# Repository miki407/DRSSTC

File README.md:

# Welcome
> **WARNING:**
> This project has not been tested yet. I cant guarantee that any of the circuits, PCBs, 3d models work or are accurate.

>This project is incomplete. The README isn't finished yet.

## Overview

This project is a tesla coil, DRSSTC to be more exact. Tesla coils are devices capable of generating extreme voltages that can be lethal if not operated correctly. 
> **Warning:** This project deals with high voltages. Replicate at your own risk.
 
 It is designed with a full bridge inverter connected to a MMC as the primary tank capacitor. This full bridge uses 4 parallel IGBT pairs driven by a single GDT. This GDT connects to the control circuit. Using a MIDI interrupter this coil has the ability to play music.

## Physical Design

The coil is designed with a skeleton topload and a vertical breakout point located in the middle of the topload. The primary coil is a pancake with a ground ring that is meant to protect it from flashover from topload.
>Note: The grounding ring is shouldn't be closed loop like shown in the image. This would short circuit the induced current and cause large current draw and energy loss.

## Circuit
The circuit for the control circuit and inverter are inspired by the UD2.7c and EasyBridge made by [Loneoceans](https://www.loneoceans.com/labs/index.htm). These circuits have been modified to fit the needs of this project.
The interactive BOM of these boards are here:
[Inverter](https://htmlpreview.github.io/?https://github.com/miki407/DRSSTC/blob/main/Full%20Bridge/Full%20Bridge/bom/ibom.html)
[Control circuit](https://htmlpreview.github.io/?https://github.com/miki407/DRSSTC/blob/main/Controller/DRSSTC%20controller/bom/ibom.html)

## Future additions

* Polyphonic MIDI interrupter
* Testing data
* Assembly guide
* Full BOM 

## Mistakes and Suggestions 
If I made any mistakes or if you want to suggest anything you can contact me on milosmilicevic575@gmail.com.

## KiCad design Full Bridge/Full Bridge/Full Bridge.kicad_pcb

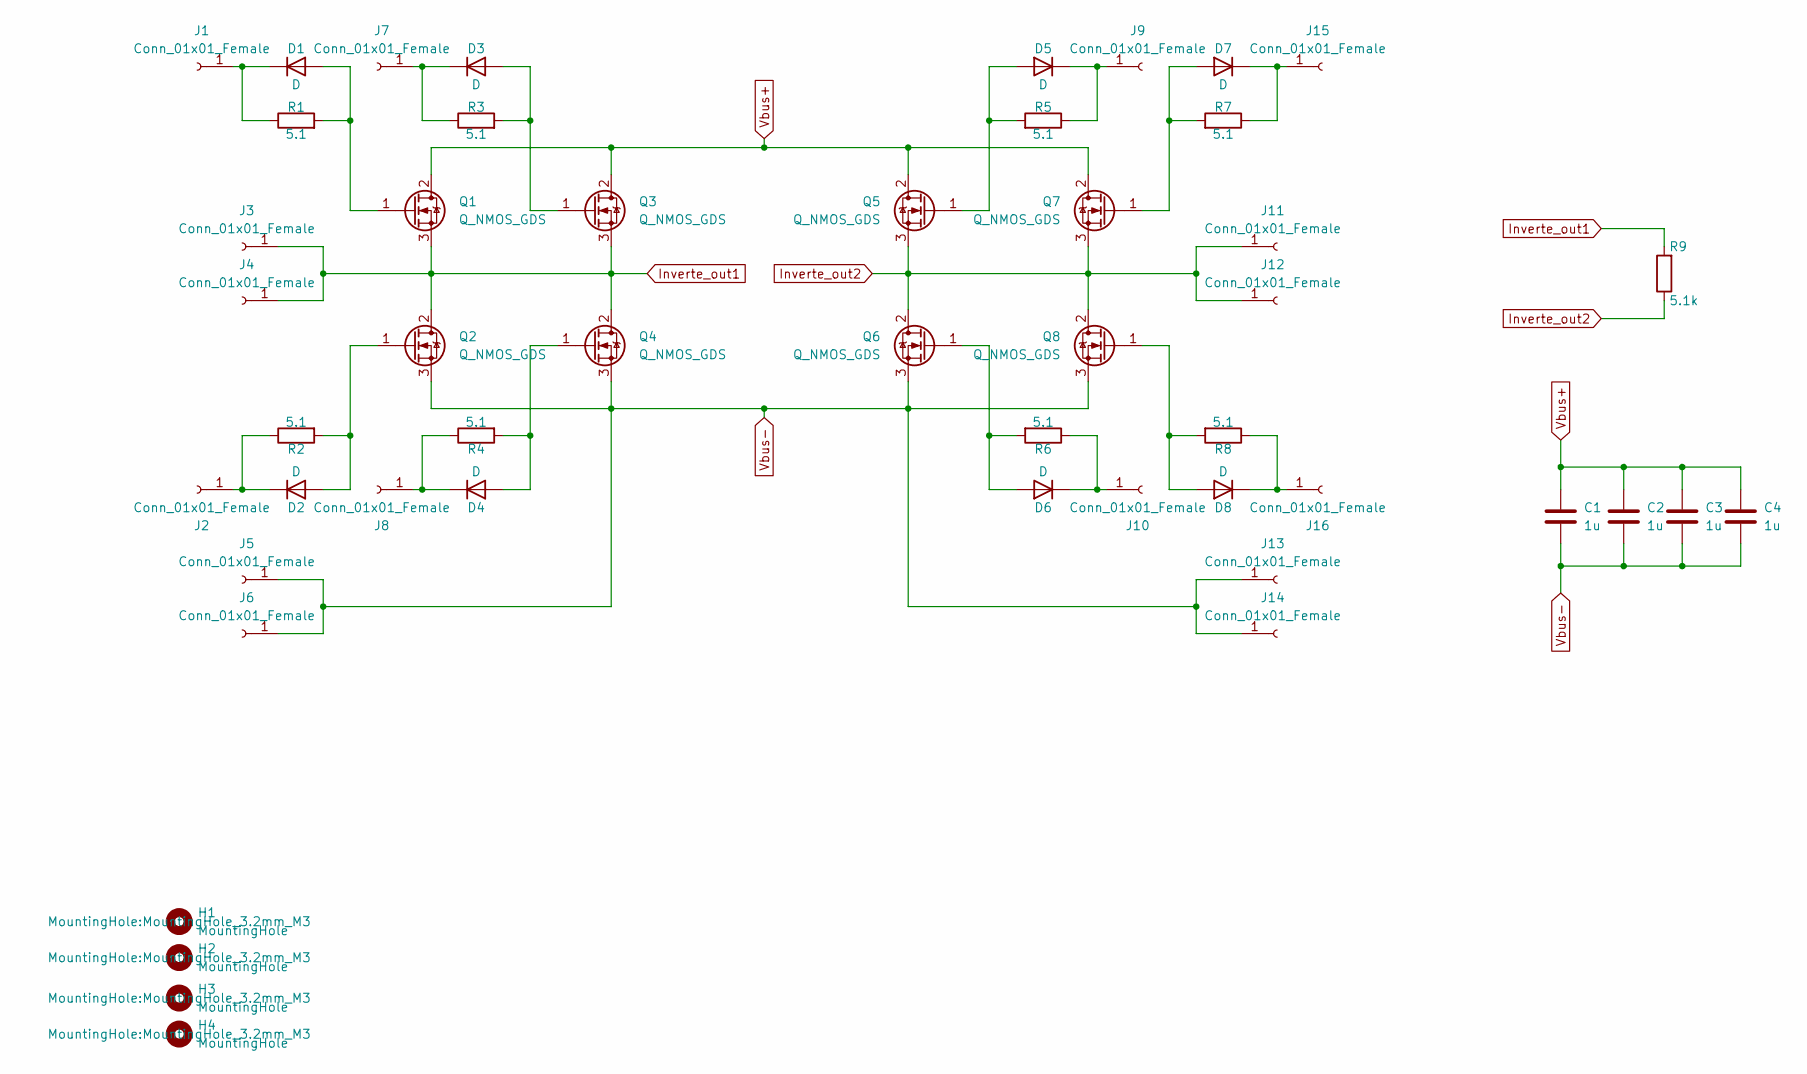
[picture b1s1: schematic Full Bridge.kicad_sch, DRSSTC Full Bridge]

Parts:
C1, C2, C3, C4: 1u; C_Rect_L24.0mm_W8.6mm_P22.50mm_MKT
D1, D2, D3, D4, D5, D6, D7, D8: D; D_SMB
H1, H2, H3, H4: MountingHole; MountingHole_3.2mm_M3
J1: Conn_01x01_Female; PinHeader_1x01_P2.54mm_Vertical
J2, J3, J4, J5, J6, J7, J8, J9, J10, J11, J12, J13, J14, J15, J16: Conn_01x01_Female; PinSocket_1x01_P2.54mm_Vertical
Q1, Q2, Q3, Q4, Q5, Q6, Q7, Q8: Q_NMOS_GDS; To-3P-SideMount
R1, R2, R3, R4, R5, R6, R7, R8: 5.1; R_1206_3216Metric
R9: 5.1k; R_Axial_Power_L20.0mm_W6.4mm_P25.40mm

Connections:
Inverte_out1: J3.1, J4.1, Q1.3 (S), Q2.2 (D), Q3.3 (S), Q4.2 (D), R9.2
Inverte_out2: J11.1, J12.1, Q5.3 (S), Q6.2 (D), Q7.3 (S), Q8.2 (D), R9.1
unnamed: D1.1 (K), J1.1, R1.1
unnamed: D1.2 (A), Q1.1 (G), R1.2
unnamed: D2.1 (K), J2.1, R2.1
unnamed: D2.2 (A), Q2.1 (G), R2.2
unnamed: D3.1 (K), J7.1, R3.1
unnamed: D3.2 (A), Q3.1 (G), R3.2
unnamed: D4.1 (K), J8.1, R4.1
unnamed: D4.2 (A), Q4.1 (G), R4.2
unnamed: D5.1 (K), J9.1, R5.1
unnamed: D5.2 (A), Q5.1 (G), R5.2
unnamed: D6.1 (K), J10.1, R6.1
unnamed: D7.1 (K), J15.1, R7.1
unnamed: D7.2 (A), Q7.1 (G), R7.2
unnamed: D8.1 (K), J16.1, R8.1
unnamed: D8.2 (A), Q8.1 (G), R8.2
unnamed: D6.2 (A), Q6.1 (G), R6.2
Vbus+: C1.1, C2.1, C3.1, C4.1, Q1.2 (D), Q3.2 (D), Q5.2 (D), Q7.2 (D)
Vbus-: C1.2, C2.2, C3.2, C4.2, J5.1, J6.1, J13.1, J14.1, Q2.3 (S), Q4.3 (S), Q6.3 (S), Q8.3 (S)

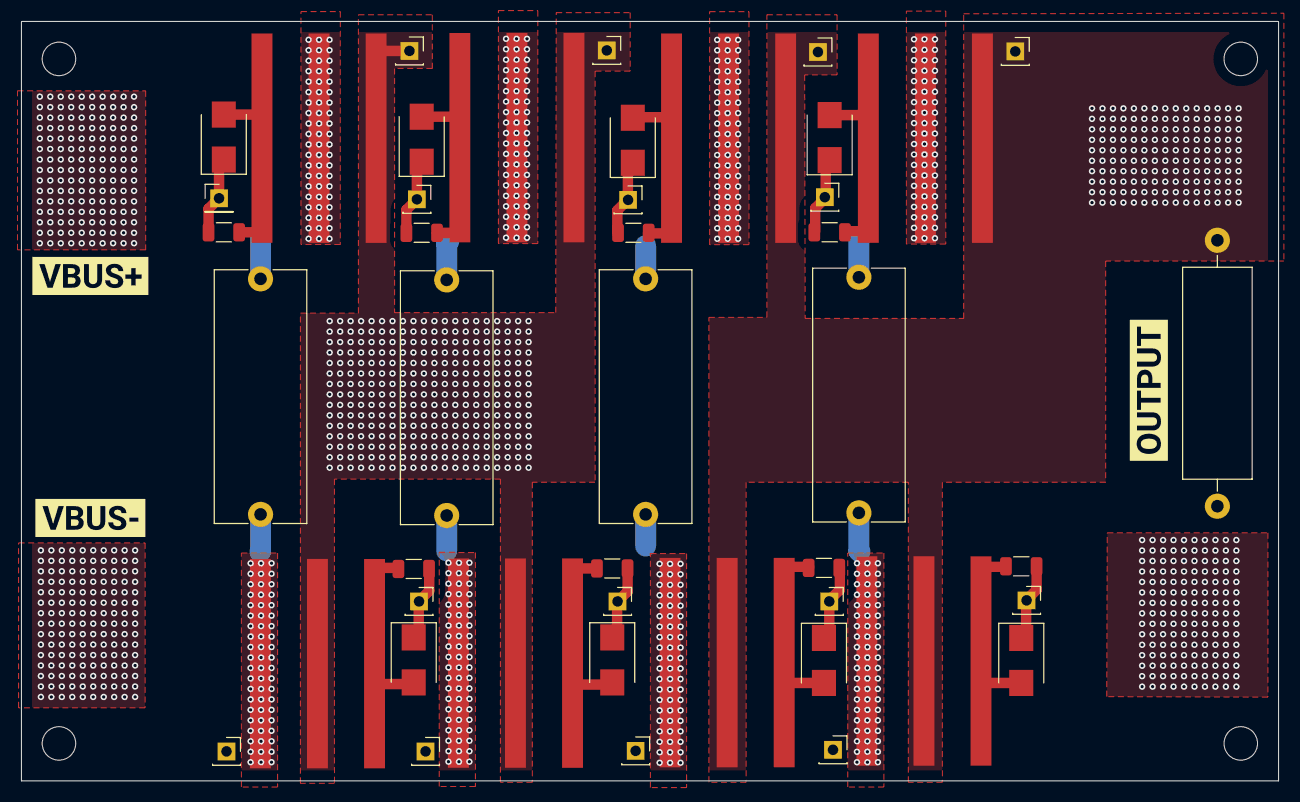
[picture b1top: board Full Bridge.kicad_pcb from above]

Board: 2 copper layers, 120.1 x 72.5 mm, 52 parts (0 on the bottom side), 20 nets.

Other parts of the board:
kibuzzard-640732BF: G***; kibuzzard-640732BF
kibuzzard-640732D0: G***; kibuzzard-640732D0
kibuzzard-640732E7: G***; kibuzzard-640732E7

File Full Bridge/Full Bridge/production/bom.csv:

Designator,Footprint,Quantity,Value,LCSC Part #
"C1, C2, C3, C4",C_Rect_L24.0mm_W8.6mm_P22.50mm_MKT,4,1u,
"D1, D2, D3, D4, D5, D6, D7, D8",D_SMB,8,D,
"H1, H2, H3, H4",MountingHole_3.2mm_M3,4,MountingHole,
"Q1, Q2, Q3, Q4, Q5, Q6, Q7, Q8",To-3P-SideMount,8,Q_NMOS_GDS,
R1,1206,1,5.1,
R2,1206,1,5.1,
R3,1206,1,5.1,
R4,1206,1,5.1,
R5,1206,1,5.1,
R6,1206,1,5.1,
R7,1206,1,5.1,
R8,1206,1,5.1,
R9,R_Axial_Power_L20.0mm_W6.4mm_P25.40mm,1,5.1k,

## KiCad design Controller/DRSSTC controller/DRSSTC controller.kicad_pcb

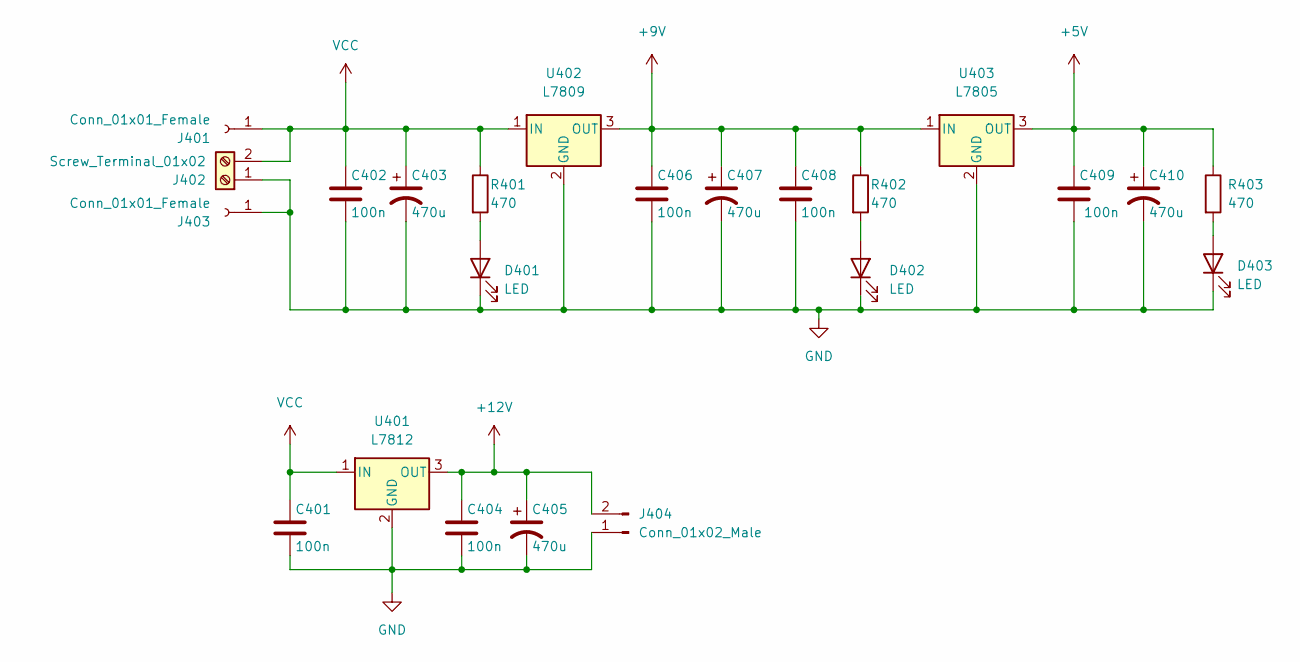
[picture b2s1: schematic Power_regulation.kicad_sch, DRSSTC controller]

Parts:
C401, C402, C404, C406, C408, C409: 100n; C_0805_2012Metric
C403: 470u; CP_Radial_D12.5mm_P5.00mm
C405, C407, C410: 470u; CP_Radial_D5.0mm_P2.50mm
D401, D402, D403: LED; LED_0805_2012Metric
J401, J403: Conn_01x01_Female; PinHeader_1x01_P2.54mm_Vertical
J402: Screw_Terminal_01x02; TerminalBlock_Phoenix_PT-1,5-2-3.5-H_1x02_P3.50mm_Horizontal
J404: Conn_01x02_Male; PinHeader_1x02_P2.54mm_Vertical
R401, R402, R403: 470; R_0805_2012Metric
U401: L7812; TO-252-2
U402: L7809; TO-252-2
U403: L7805; TO-252-2

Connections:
+5V: C409.1, C410.1, R403.1, U403.3 (OUT); also elsewhere on the board
+9V: C406.1, C407.1, C408.1, R402.1, U402.3 (OUT), U403.1 (IN); also elsewhere on the board
+12V: C404.1, C405.1, J404.2, U401.3 (OUT)
GND: C401.2, C402.2, C403.2, C404.2, C405.2, C406.2, C407.2, C408.2, C409.2, C410.2, D401.1 (K), D402.1 (K), D403.1 (K), J402.1, J403.1, J404.1, U401.2 (GND), U402.2 (GND), U403.2 (GND); also elsewhere on the board
unnamed: D401.2 (A), R401.2
unnamed: D402.2 (A), R402.2
unnamed: D403.2 (A), R403.2
VCC: C401.1, C402.1, C403.1, J401.1, J402.2, R401.1, U401.1 (IN), U402.1 (IN); also elsewhere on the board

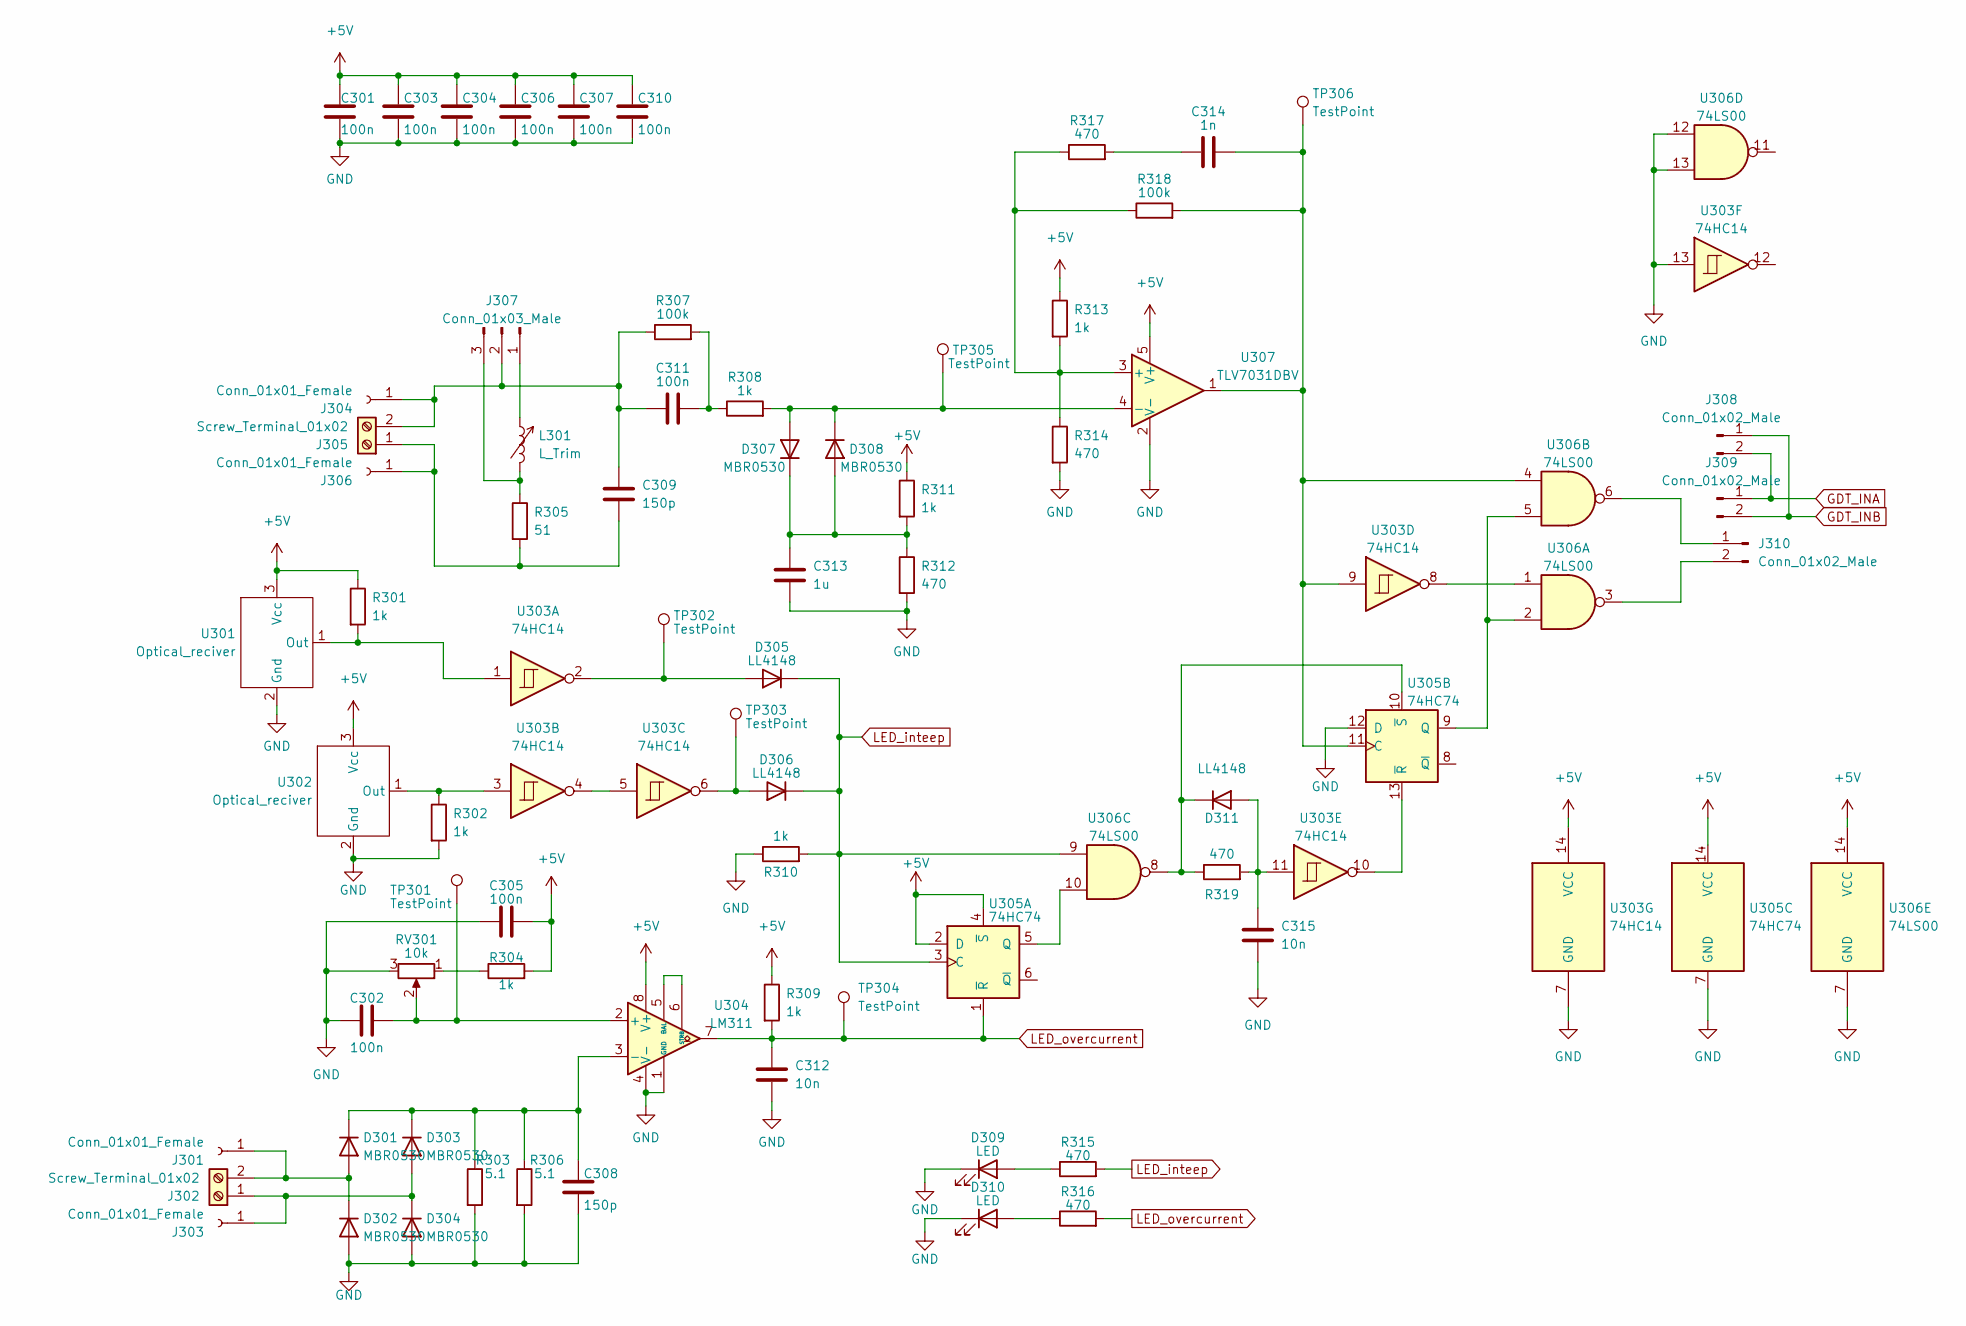
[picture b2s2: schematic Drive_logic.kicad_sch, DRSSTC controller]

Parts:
C301, C302, C303, C304, C305, C306, C307, C310, C311: 100n; C_0805_2012Metric
C308, C309: 150p; C_0805_2012Metric
C312, C315: 10n; C_0805_2012Metric
C313: 1u; C_0805_2012Metric
C314: 1n; C_0805_2012Metric
D301, D302, D303, D304, D307, D308: MBR0530; D_0805_2012Metric
D305, D306, D311: LL4148; D_0805_2012Metric
D309, D310: LED; LED_0805_2012Metric
J301, J303, J304, J306: Conn_01x01_Female; PinHeader_1x01_P2.54mm_Vertical
J302, J305: Screw_Terminal_01x02; TerminalBlock_Phoenix_PT-1,5-2-3.5-H_1x02_P3.50mm_Horizontal
J307: Conn_01x03_Male; PinHeader_1x03_P2.54mm_Vertical
J308, J309, J310: Conn_01x02_Male; PinHeader_1x02_P2.54mm_Vertical
L301: L_Trim; L_Radial_D7.5mm_P5.00mm_Fastron_07P
R301, R302, R304, R308, R309, R310, R311, R313: 1k; R_0805_2012Metric
R303, R306: 5.1; R_2010_5025Metric
R305: 51; R_Axial_Power_L25.0mm_W9.0mm_P27.94mm
R307, R318: 100k; R_0805_2012Metric
R312, R314, R315, R316, R317, R319: 470; R_0805_2012Metric
RV301: 10k; Potentiometer_Bourns_3266Z_Horizontal
TP301, TP302, TP303, TP304, TP305, TP306: TestPoint; TestPoint_Loop_D2.50mm_Drill1.0mm
U301, U302: Optical_reciver; PLT135
U303: 74HC14; SO-14_3.9x8.65mm_P1.27mm
U304: LM311; SO-8_3.9x4.9mm_P1.27mm
U305: 74HC74; SO-14_3.9x8.65mm_P1.27mm
U306: 74LS00; SO-14_3.9x8.65mm_P1.27mm
U307: TLV7031DBV; SOT-23-5

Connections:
+5V: C301.1, C303.1, C304.1, C305.2, C306.1, C307.1, C310.1, R301.1, R304.2, R309.1, R311.1, R313.1, U301.3 (Vcc), U302.3 (Vcc), U303.14 (VCC), U304.8 (V+), U305.2 (D), U305.4 (~S), U305.14 (VCC), U306.14 (VCC), U307.5 (V+); also elsewhere on the board
GDT_INA: J308.2, J309.1; also elsewhere on the board
GDT_INB: J308.1, J309.2; also elsewhere on the board
GND: C301.2, C302.1, C303.2, C304.2, C305.1, C306.2, C307.2, C308.2, C310.2, C312.2, C313.2, C315.2, D302.2 (A), D304.2 (A), D309.1 (K), D310.1 (K), R302.2, R303.2, R306.2, R310.1, R312.2, R314.2, RV301.3, U301.2 (Gnd), U302.2 (Gnd), U303.7 (GND), U303.13, U304.1 (GND), U304.4 (V-), U305.7 (GND), U305.12 (D), U306.7 (GND), U306.12, U306.13, U307.2 (V-); also elsewhere on the board
LED_inteep: D305.1 (K), D306.1 (K), R310.2, R315.2, U305.3 (C), U306.9
LED_overcurrent: C312.1, R309.2, R316.2, TP304.1, U304.7, U305.1 (~R)
unnamed: C311.2, R307.2, R308.1
unnamed: C314.1, R317.2
unnamed: D301.2 (A), D302.1 (K), J301.1, J302.2
unnamed: C308.1, D301.1 (K), D303.1 (K), R303.1, R306.1, U304.3 (-)
unnamed: D303.2 (A), D304.1 (K), J302.1, J303.1
unnamed: D305.2 (A), TP302.1, U303.2
unnamed: D306.2 (A), TP303.1, U303.6
unnamed: D307.2 (A), D308.1 (K), R308.2, TP305.1, U307.4 (-)
unnamed: C313.1, D307.1 (K), D308.2 (A), R311.2, R312.1
unnamed: D309.2 (A), R315.1
unnamed: D310.2 (A), R316.1
unnamed: C315.1, D311.2 (A), R319.2, U303.11
unnamed: D311.1 (K), R319.1, U305.10 (~S), U306.8
unnamed: C309.1, C311.1, J304.1, J305.2, J307.2, R307.1
unnamed: C309.2, J305.1, J306.1, R305.2
unnamed: J307.1, L301.1
unnamed: J307.3, L301.2, R305.1
unnamed: J310.1, U306.6
unnamed: J310.2, U306.3
unnamed: R304.1, RV301.1
unnamed: R301.2, U301.1 (Out), U303.1
unnamed: R302.1, U302.1 (Out), U303.3
unnamed: U303.4, U303.5
unnamed: U303.8, U306.1
unnamed: C302.2, RV301.2, TP301.1, U304.2 (+)
unnamed: U304.5 (BAL), U304.6 (STRB)
unnamed: U305.5 (Q), U306.10
unnamed: C314.2, R318.2, TP306.1, U303.9, U305.11 (C), U306.4, U307.1
unnamed: U305.9 (Q), U306.2, U306.5
unnamed: U303.10, U305.13 (~R)
unnamed: R313.2, R314.1, R317.1, R318.1, U307.3 (+)

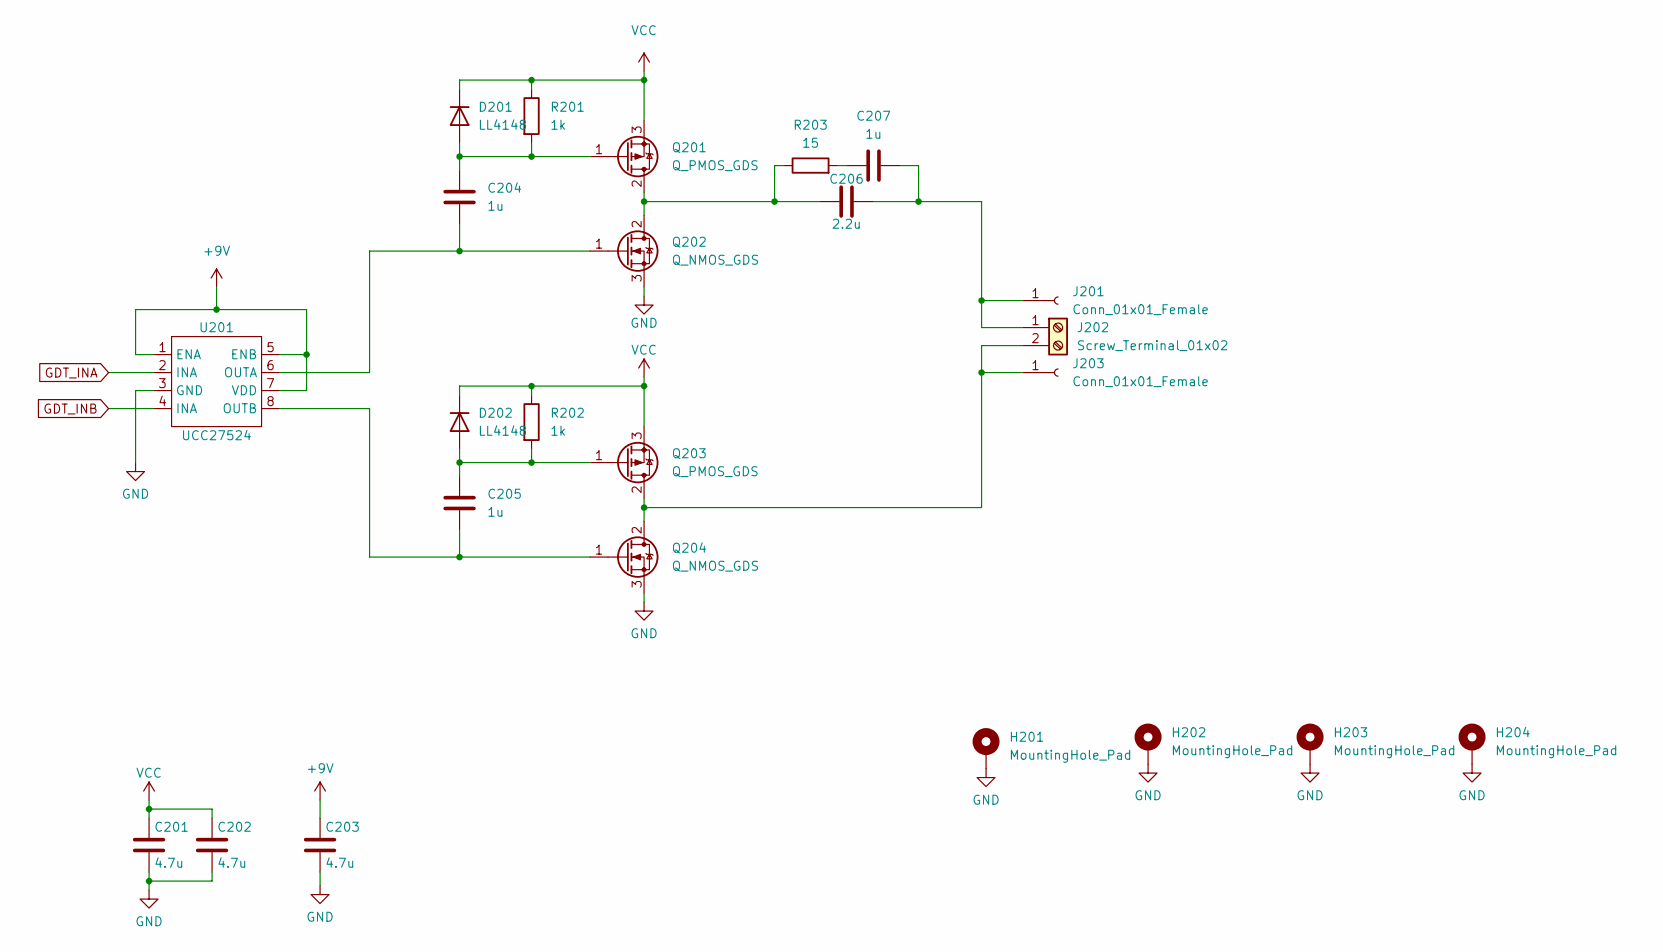
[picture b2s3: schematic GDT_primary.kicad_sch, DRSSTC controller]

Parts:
C201, C202, C203: 4.7u; C_1206_3216Metric
C204, C205, C207: 1u; C_0805_2012Metric
C206: 2.2u; C_2220_5650Metric
D201, D202: LL4148; D_MiniMELF
H201, H202, H203, H204: MountingHole_Pad; MountingHole_3.2mm_M3_Pad_Via
J201, J203: Conn_01x01_Female; PinHeader_1x01_P2.54mm_Vertical
J202: Screw_Terminal_01x02; TerminalBlock_Phoenix_PT-1,5-2-3.5-H_1x02_P3.50mm_Horizontal
Q201, Q203: Q_PMOS_GDS; TO-252-2
Q202, Q204: Q_NMOS_GDS; TO-252-2
R201, R202: 1k; R_0805_2012Metric
R203: 15; R_0805_2012Metric
U201: UCC27524; SOIC-8_3.9x4.9mm_P1.27mm

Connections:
+9V: C203.1, U201.1 (ENA), U201.5 (ENB), U201.7 (VDD); also elsewhere on the board
GDT_INA: U201.2 (INA); also elsewhere on the board
GDT_INB: U201.4 (INA); also elsewhere on the board
GND: C201.2, C202.2, C203.2, H201.1, H202.1, H203.1, H204.1, Q202.3 (S), Q204.3 (S), U201.3 (GND); also elsewhere on the board
unnamed: C207.1, R203.2
unnamed: C204.1, D201.2 (A), Q201.1 (G), R201.2
unnamed: C205.1, D202.2 (A), Q203.1 (G), R202.2
unnamed: C206.2, C207.2, J201.1, J202.1
unnamed: J202.2, J203.1, Q203.2 (D), Q204.2 (D)
unnamed: C206.1, Q201.2 (D), Q202.2 (D), R203.1
unnamed: C204.2, Q202.1 (G), U201.6 (OUTA)
unnamed: C205.2, Q204.1 (G), U201.8 (OUTB)
VCC: C201.1, C202.1, D201.1 (K), D202.1 (K), Q201.3 (S), Q203.3 (S), R201.1, R202.1; also elsewhere on the board

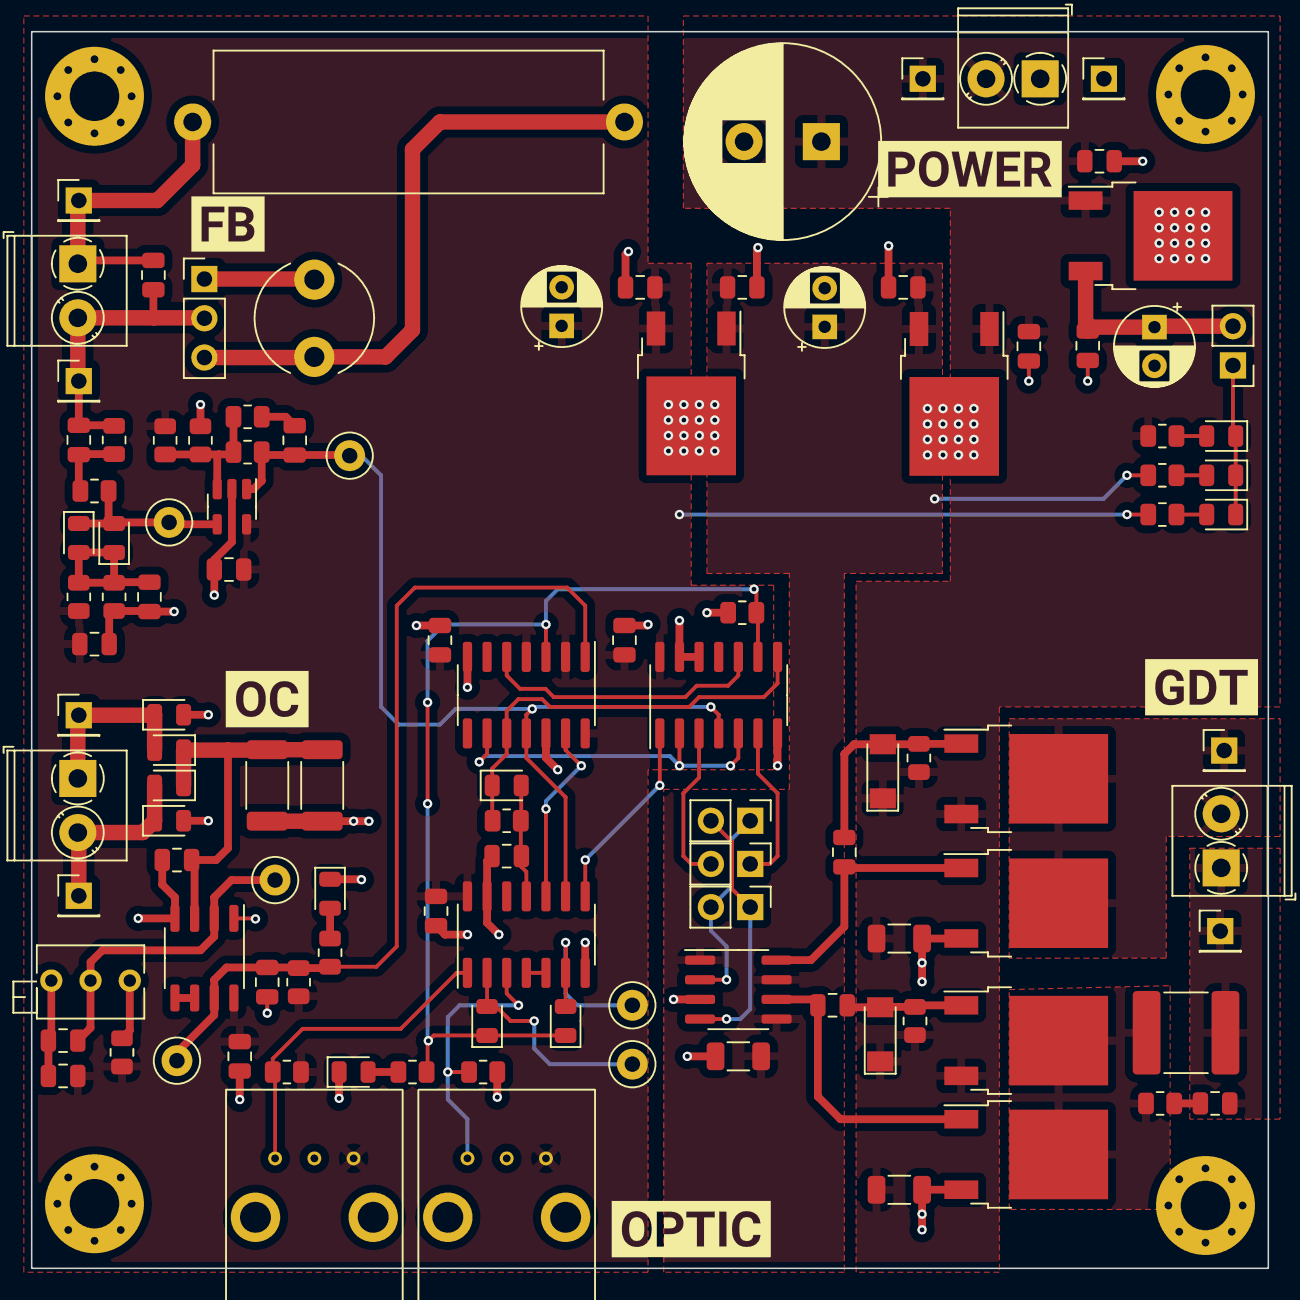
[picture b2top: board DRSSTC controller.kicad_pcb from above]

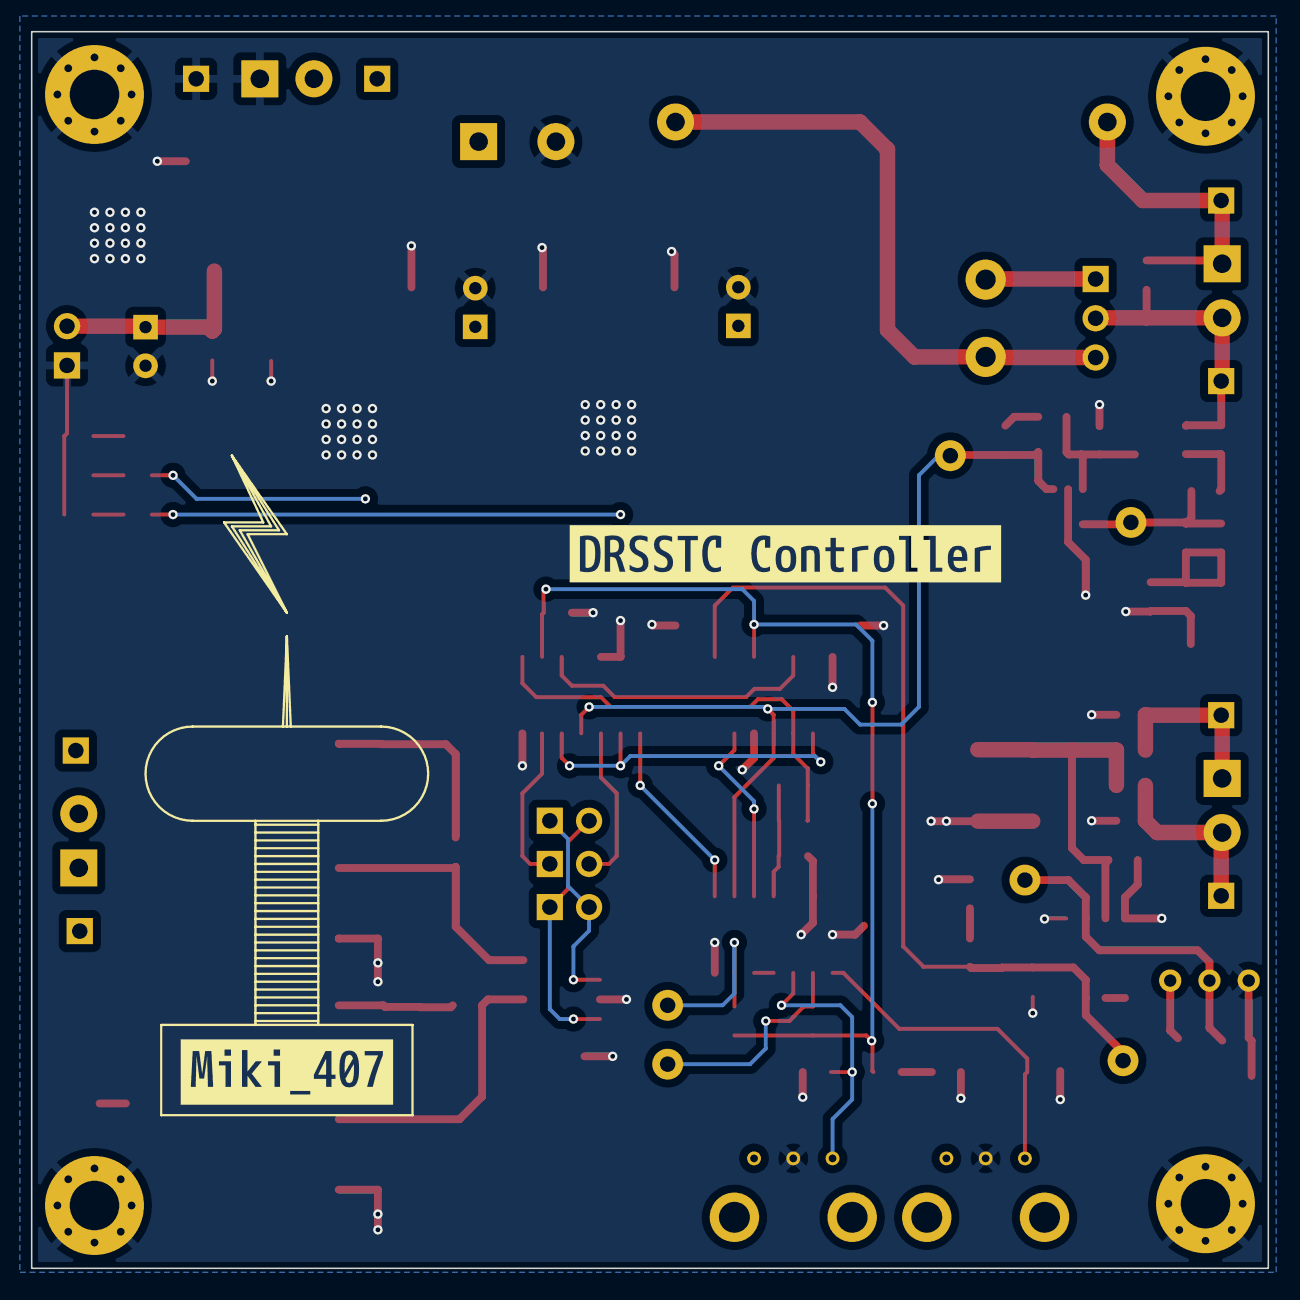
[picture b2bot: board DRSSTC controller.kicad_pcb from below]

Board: 2 copper layers, 80.0 x 80.0 mm, 124 parts (2 on the bottom side), 51 nets.

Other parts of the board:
kibuzzard-64072E6F: G***; kibuzzard-64072E6F
kibuzzard-64072E9F: G***; kibuzzard-64072E9F
kibuzzard-64072E65: G***; kibuzzard-64072E65
kibuzzard-64072E85: G***; kibuzzard-64072E85
kibuzzard-64072EC9: G***; kibuzzard-64072EC9
kibuzzard-64121B21: G***; kibuzzard-64121B21
kibuzzard-6412189F: G***; kibuzzard-6412189F

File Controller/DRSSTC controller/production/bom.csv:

Designator,Footprint,Quantity,Value,LCSC Part #
C201,1206,1,4.7u,
C202,1206,1,4.7u,
C203,1206,1,4.7u,
C204,0805,1,1u,
C205,0805,1,1u,
C206,2220,1,2.2u,
C207,0805,1,1u,
C301,0805,1,100n,
C302,0805,1,100n,
C303,0805,1,100n,
C304,0805,1,100n,
C305,0805,1,100n,
C306,0805,1,100n,
C307,0805,1,100n,
C308,0805,1,150p,
C309,0805,1,150p,
C310,0805,1,100n,
C311,0805,1,100n,
C312,0805,1,10n,
C313,0805,1,1u,
C314,0805,1,1n,
C315,0805,1,10n,
C401,0805,1,100n,
C402,0805,1,100n,
C403,CP_Radial_D12.5mm_P5.00mm,1,470u,
C404,0805,1,100n,
"C405, C407, C410",CP_Radial_D5.0mm_P2.50mm,3,470u,
C406,0805,1,100n,
C408,0805,1,100n,
C409,0805,1,100n,
"D201, D202",D_MiniMELF,2,LL4148,
D301,0805,1,MBR0530,
D302,0805,1,MBR0530,
D303,0805,1,MBR0530,
D304,0805,1,MBR0530,
D305,0805,1,LL4148,
D306,0805,1,LL4148,
D307,0805,1,MBR0530,
D308,0805,1,MBR0530,
D309,0805,1,LED,
D310,0805,1,LED,
D311,0805,1,LL4148,
D401,0805,1,LED,
D402,0805,1,LED,
D403,0805,1,LED,
"H201, H202, H203, H204",MountingHole_3.2mm_M3_Pad_Via,4,MountingHole_Pad,
"J201, J203, J301, J303, J304, J306, J401, J403",PinHeader_1x01_P2.54mm_Vertical,8,Conn_01x01_Female,
"J202, J302, J305, J402","TerminalBlock_Phoenix_PT-1,5-2-3.5-H_1x02_P3.50mm_Horizontal",4,Screw_Terminal_01x02,
J307,PinHeader_1x03_P2.54mm_Vertical,1,Conn_01x03_Male,
"J308, J309, J310, J404",PinHeader_1x02_P2.54mm_Vertical,4,Conn_01x02_Male,
L301,L_Radial_D7.5mm_P5.00mm_Fastron_07P,1,L_Trim,
"Q201, Q203",TO-252-2,2,Q_PMOS_GDS,
"Q202, Q204",TO-252-2,2,Q_NMOS_GDS,
R201,0805,1,1k,
R202,0805,1,1k,
R203,0805,1,15,
R301,0805,1,1k,
R302,0805,1,1k,
R303,2010,1,5.1,
R304,0805,1,1k,
R305,R_Axial_Power_L25.0mm_W9.0mm_P27.94mm,1,51,
R306,2010,1,5.1,
R307,0805,1,100k,
R308,0805,1,1k,
R309,0805,1,1k,
R310,0805,1,1k,
R311,0805,1,1k,
R312,0805,1,470,
R313,0805,1,1k,
R314,0805,1,470,
R315,0805,1,470,
R316,0805,1,470,
R317,0805,1,470,
R318,0805,1,100k,
R319,0805,1,470,
R401,0805,1,470,
R402,0805,1,470,
R403,0805,1,470,
RV301,Potentiometer_Bourns_3266Z_Horizontal,1,10k,
"TP301, TP302, TP303, TP304, TP305, TP306",TestPoint_Loop_D2.50mm_Drill1.0mm,6,TestPoint,
U201,SOIC-8_3.9x4.9mm_P1.27mm,1,UCC27524,
"U301, U302",PLT135,2,Optical_reciver,
U303,SO-14_3.9x8.65mm_P1.27mm,1,74HC14,
U304,SO-8_3.9x4.9mm_P1.27mm,1,LM311,
U305,SO-14_3.9x8.65mm_P1.27mm,1,74HC74,
U306,SO-14_3.9x8.65mm_P1.27mm,1,74LS00,
U307,SOT-23-5,1,TLV7031DBV,
U401,TO-252-2,1,L7812,
U402,TO-252-2,1,L7809,
U403,TO-252-2,1,L7805,

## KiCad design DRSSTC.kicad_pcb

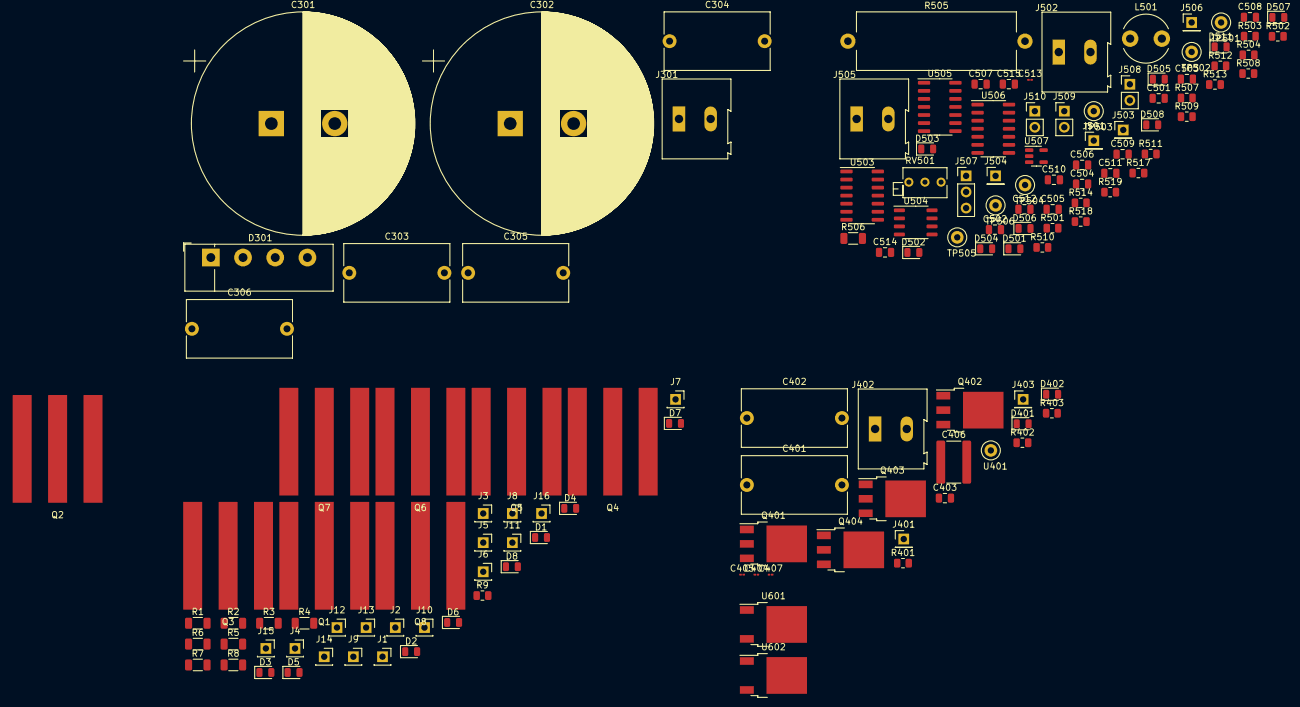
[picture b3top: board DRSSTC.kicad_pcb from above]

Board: 2 copper layers, 135 parts (0 on the bottom side), 68 nets, no tracks yet.

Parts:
C301, C302: 480u; CP_Radial_D35.0mm_P10.00mm_SnapIn
C303, C304, C305, C306, C401, C402: 4.7u; C_Rect_L16.5mm_W9.0mm_P15.00mm_MKT
C403, C501, C502, C503, C504, C505, C506, C507, C510, C511: 100n; C_0805_2012Metric
C404, C405, C407, C513: 1u; C_01005_0402Metric
C406: 2.2u; C_1825_4564Metric
C508, C509: 150p; C_0805_2012Metric
C512, C515: 10n; C_0805_2012Metric
C514: 1n; C_0805_2012Metric
D1, D2, D3, D4, D5, D6, D7, D8, D401, D402: D; D_0805_2012Metric
D301: D_Bridge_+AA-; Diode_Bridge_Vishay_KBU
D501, D502, D503, D504, D507, D508: MBR0530; D_0805_2012Metric
D505, D506, D511: LL4148; D_0805_2012Metric
J1, J2, J3, J4, J5, J6, J7, J8, J9, J10, J11, J12, J13, J14, J15, J16: Conn_01x01_Female; PinSocket_1x01_P2.54mm_Vertical
J301, J402, J502, J505: Screw_Terminal_01x02; TerminalBlock_Altech_AK300-2_P5.00mm
J401, J403, J501, J503, J504, J506: Conn_01x01_Female; PinHeader_1x01_P2.54mm_Vertical
J507: Conn_01x03_Male; PinHeader_1x03_P2.54mm_Vertical
J508, J509, J510: Conn_01x02_Male; PinHeader_1x02_P2.54mm_Vertical
L501: L_Trim; L_Radial_D7.5mm_P5.00mm_Fastron_07P
Q1, Q2, Q3, Q4, Q5, Q6, Q7, Q8: Q_NMOS_GDS; TO-3P-SideMount
Q401, Q403: Q_PMOS_GDS; TO-252-3_TabPin2
Q402, Q404: Q_NMOS_GDS; TO-252-3_TabPin2
R1, R2, R3, R4, R5, R6, R7, R8, R506: 5.1; R_1206_3216Metric
R9: 5.1k; R_0805_2012Metric
R401, R402, R501, R502, R504, R508, R509, R510, R511, R513: 1k; R_0805_2012Metric
R403: 15; R_0805_2012Metric
R503: 5.1; R_0805_2012Metric
R505: 51; R_Axial_Power_L25.0mm_W9.0mm_P27.94mm
R507, R518: 100k; R_0805_2012Metric
R512, R514, R517, R519: 470; R_0805_2012Metric
RV501: 19k; Potentiometer_Bourns_3266Z_Horizontal
TP501, TP502, TP503, TP504, TP505, TP506: TestPoint; TestPoint_Loop_D2.50mm_Drill1.0mm
U401: UCC27524; TestPoint_Loop_D2.50mm_Drill1.0mm
U503: 74HC14; SO-14_3.9x8.65mm_P1.27mm
U504: LM311; SO-8_3.9x4.9mm_P1.27mm
U505: 74HC74; SO-14_3.9x8.65mm_P1.27mm
U506: 74LS00; SO-14_3.9x8.65mm_P1.27mm
U507: TLV7031DBV; SOT-23-5
U601: L7809; TO-252-2
U602: L7805; TO-252-2

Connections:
+5V: C501.1, C503.1, C504.1, C505.2, C506.1, C507.1, C510.1, R501.1, R504.2, R509.1, R511.1, R513.1, U503.14 (VCC), U504.8 (V+), U505.2 (D), U505.4 (~S), U505.14 (VCC), U506.14 (VCC), U507.5 (V+), U602.3 (OUT)
+9V: C403.1, U401.1 (ENA), U601.3 (OUT), U602.1 (IN)
GDT_INA: J508.2, J509.1
GDT_INB: J508.1, J509.2
GND: C401.2, C402.2, C403.2, C501.2, C502.1, C503.2, C504.2, C505.1, C506.2, C507.2, C508.2, C510.2, C512.2, C513.2, C515.2, D502.2 (A), D504.2 (A), Q402.3 (S), Q404.3 (S), R502.2, R503.2, R506.2, R510.1, R512.2, R514.2, RV501.3, U503.7 (GND), U503.13, U504.1 (GND), U504.4 (V-), U505.7 (GND), U505.12 (D), U506.7 (GND), U506.12, U506.13, U507.2 (V-)
Inverte_out1: J3.1, J4.1, Q1.3 (S), Q2.2 (D), Q3.3 (S), Q4.2 (D), R9.2
Inverte_out2: J11.1, J12.1, Q5.3 (S), Q6.2 (D), Q7.3 (S), Q8.2 (D), R9.1
LED_inteep: D505.1 (K), D506.1 (K), R510.2, U505.3 (C), U506.9
LED_overcurrent: C512.1, R509.2, TP504.1, U504.7, U505.1 (~R)
unnamed: C404.1, D401.2 (A), Q401.1 (G), R401.2
unnamed: C404.2, Q402.1 (G)
unnamed: C405.1, D402.2 (A), Q403.1 (G), R402.2
unnamed: C405.2, Q404.1 (G)
unnamed: C406.1, Q401.2 (D), Q402.2 (D), R403.1
unnamed: C406.2, C407.2, J401.1, J402.1
unnamed: C407.1, R403.2
unnamed: C502.2, RV501.2, TP501.1, U504.2 (+)
unnamed: C508.1, D501.1 (K), D503.1 (K), R503.1, R506.1, U504.3 (-)
unnamed: C509.1, C511.1, J504.1, J505.2, J507.2, R507.1
unnamed: C509.2, J505.1, J506.1, R505.2
unnamed: C511.2, R507.2, R508.1
unnamed: C513.1, D507.1 (K), D508.2 (A), R511.2, R512.1
unnamed: C514.1, R517.2
unnamed: C514.2, R518.2, TP506.1, U503.9, U505.11 (C), U506.4, U507.1
unnamed: C515.1, D511.2 (A), R519.2, U503.11
unnamed: U601.2 (GND), U602.2 (GND)
unnamed: D1.1 (K), J1.1, R1.1
unnamed: D1.2 (A), Q1.1 (G), R1.2
unnamed: D2.1 (K), J2.1, R2.1
unnamed: D2.2 (A), Q2.1 (G), R2.2
unnamed: D3.1 (K), J7.1, R3.1
unnamed: D3.2 (A), Q3.1 (G), R3.2
unnamed: D4.1 (K), J8.1, R4.1
unnamed: D4.2 (A), Q4.1 (G), R4.2
unnamed: D5.1 (K), J9.1, R5.1
unnamed: D5.2 (A), Q5.1 (G), R5.2
unnamed: D6.1 (K), J10.1, R6.1
unnamed: D6.2 (A), Q6.1 (G), R6.2
unnamed: D7.1 (K), J15.1, R7.1
unnamed: D7.2 (A), Q7.1 (G), R7.2
unnamed: D8.1 (K), J16.1, R8.1
unnamed: D8.2 (A), Q8.1 (G), R8.2
unnamed: D301.2, J301.2
unnamed: D301.3, J301.1
unnamed: D501.2 (A), D502.1 (K), J501.1, J502.2
unnamed: D503.2 (A), D504.1 (K), J502.1, J503.1
unnamed: D505.2 (A), TP502.1, U503.2
unnamed: D506.2 (A), TP503.1, U503.6
unnamed: D507.2 (A), D508.1 (K), R508.2, TP505.1, U507.4 (-)
unnamed: D511.1 (K), R519.1, U505.10 (~S), U506.8
unnamed: J402.2, J403.1, Q403.2 (D), Q404.2 (D)
unnamed: J507.1, L501.1
unnamed: J507.3, L501.2, R505.1
unnamed: J510.1, U506.6
unnamed: J510.2, U506.3
unnamed: R501.2, U503.1
unnamed: R502.1, U503.3
unnamed: R504.1, RV501.1
unnamed: R513.2, R514.1, R517.1, R518.1, U507.3 (+)
unnamed: U503.4, U503.5
unnamed: U503.8, U506.1
unnamed: U503.10, U505.13 (~R)
unnamed: U504.5 (BAL), U504.6 (STRB)
unnamed: U505.5 (Q), U506.10
unnamed: U505.9 (Q), U506.2, U506.5
VCC: C401.1, C402.1, D401.1 (K), D402.1 (K), Q401.3 (S), Q403.3 (S), R401.1, R402.1, U601.1 (IN)
Vbus+: C301.1, C302.1, C303.1, C304.1, C305.1, C306.1, D301.1 (+), Q1.2 (D), Q3.2 (D), Q5.2 (D), Q7.2 (D)
Vbus-: C301.2, C302.2, C303.2, C304.2, C305.2, C306.2, D301.4 (-), J5.1, J6.1, J13.1, J14.1, Q2.3 (S), Q4.3 (S), Q6.3 (S), Q8.3 (S)

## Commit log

2023-03-01 0.1V control-circuit
    Next relese:
    Mounting holes;
    Fan header;
    Better layout;
    Bigger capacitors;
2023-03-01 V0.15a
2023-03-06 v0.15b
2023-03-07 V0.15c
2023-03-07 v0.15d
2023-03-07 V0.2a
2023-03-07 v0.2b
2023-03-09 V0.2c
    Added stl files
    PCB update
2023-03-09 V0.2d
2023-03-09 Created README
2023-03-11 added 3d model
2023-03-15 Updated circuit
2023-03-15 Updated Production Files
